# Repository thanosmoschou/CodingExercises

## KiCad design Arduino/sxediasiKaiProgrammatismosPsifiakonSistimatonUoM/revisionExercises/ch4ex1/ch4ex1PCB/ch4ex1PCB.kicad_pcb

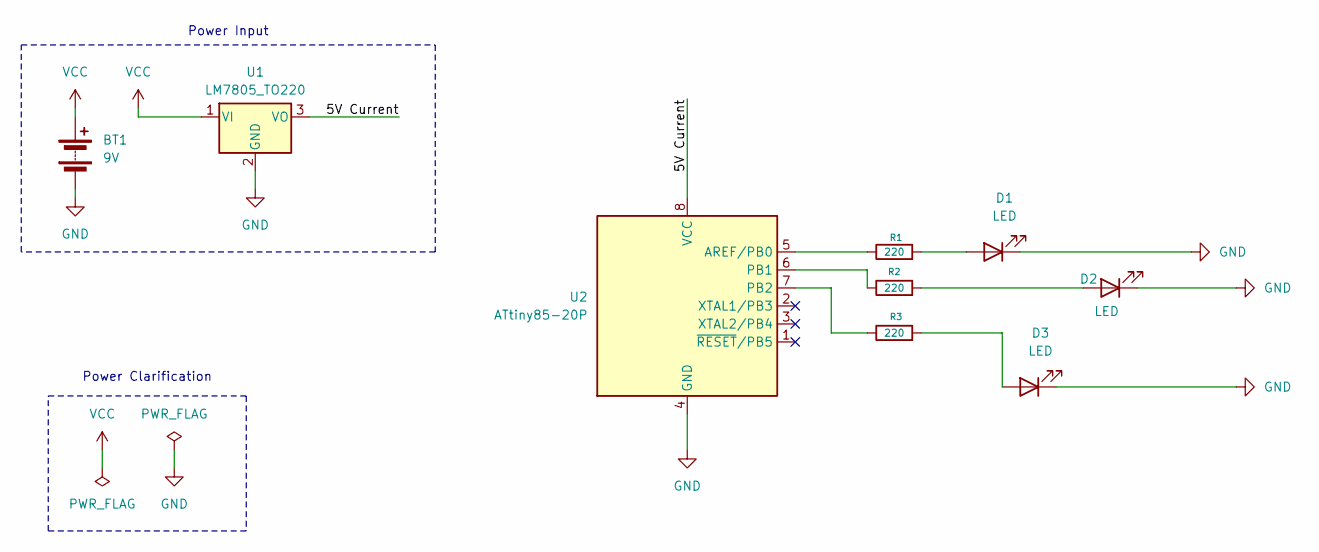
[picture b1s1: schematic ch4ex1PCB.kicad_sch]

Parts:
BT1: 9V; BatteryHolder_MPD_BA9VPC_1xPP3
D1, D2, D3: LED; LED_D5.0mm_Clear
R1, R2, R3: 220; R_Axial_DIN0207_L6.3mm_D2.5mm_P10.16mm_Horizontal
U1: LM7805_TO220; TO-220-3_Vertical
U2: ATtiny85-20P; DIP-8_W7.62mm

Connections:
/5V Current: U1.3 (VO), U2.8 (VCC)
GND: BT1.2 (-), D1.1 (K), D2.1 (K), D3.1 (K), U1.2 (GND), U2.4 (GND)
unnamed: D1.2 (A), R1.2
unnamed: D2.2 (A), R2.2
unnamed: D3.2 (A), R3.2
unnamed: R1.1, U2.5 (AREF/PB0)
unnamed: R2.1, U2.6 (PB1)
unnamed: R3.1, U2.7 (PB2)
VCC: BT1.1 (+), U1.1 (VI)

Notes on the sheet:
Power Clarification
Power Input

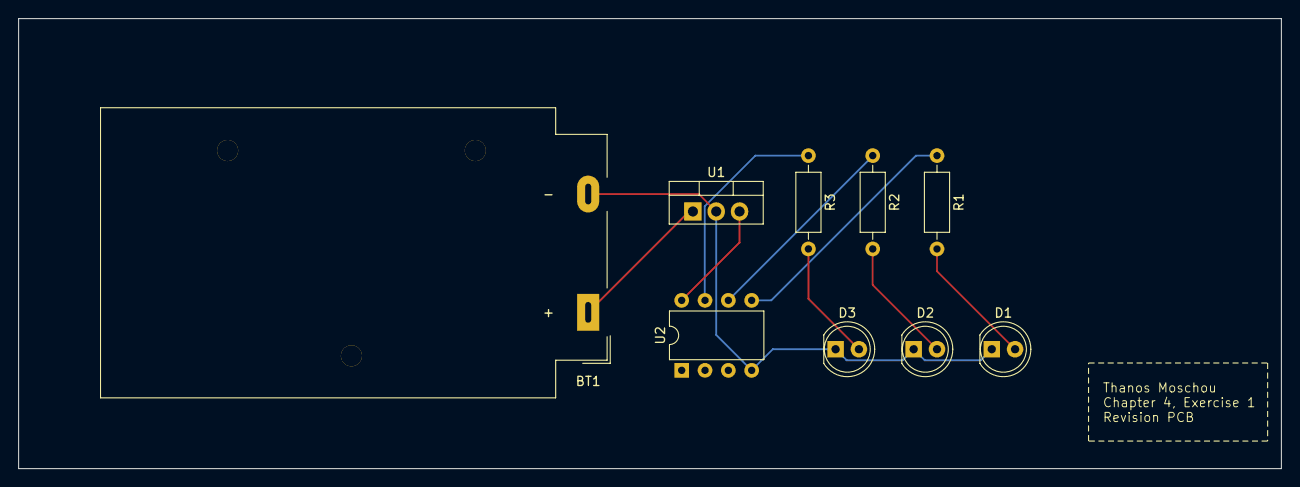
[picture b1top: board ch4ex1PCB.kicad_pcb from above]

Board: 2 copper layers, 137.5 x 49.0 mm, 9 parts (0 on the bottom side), 9 nets.

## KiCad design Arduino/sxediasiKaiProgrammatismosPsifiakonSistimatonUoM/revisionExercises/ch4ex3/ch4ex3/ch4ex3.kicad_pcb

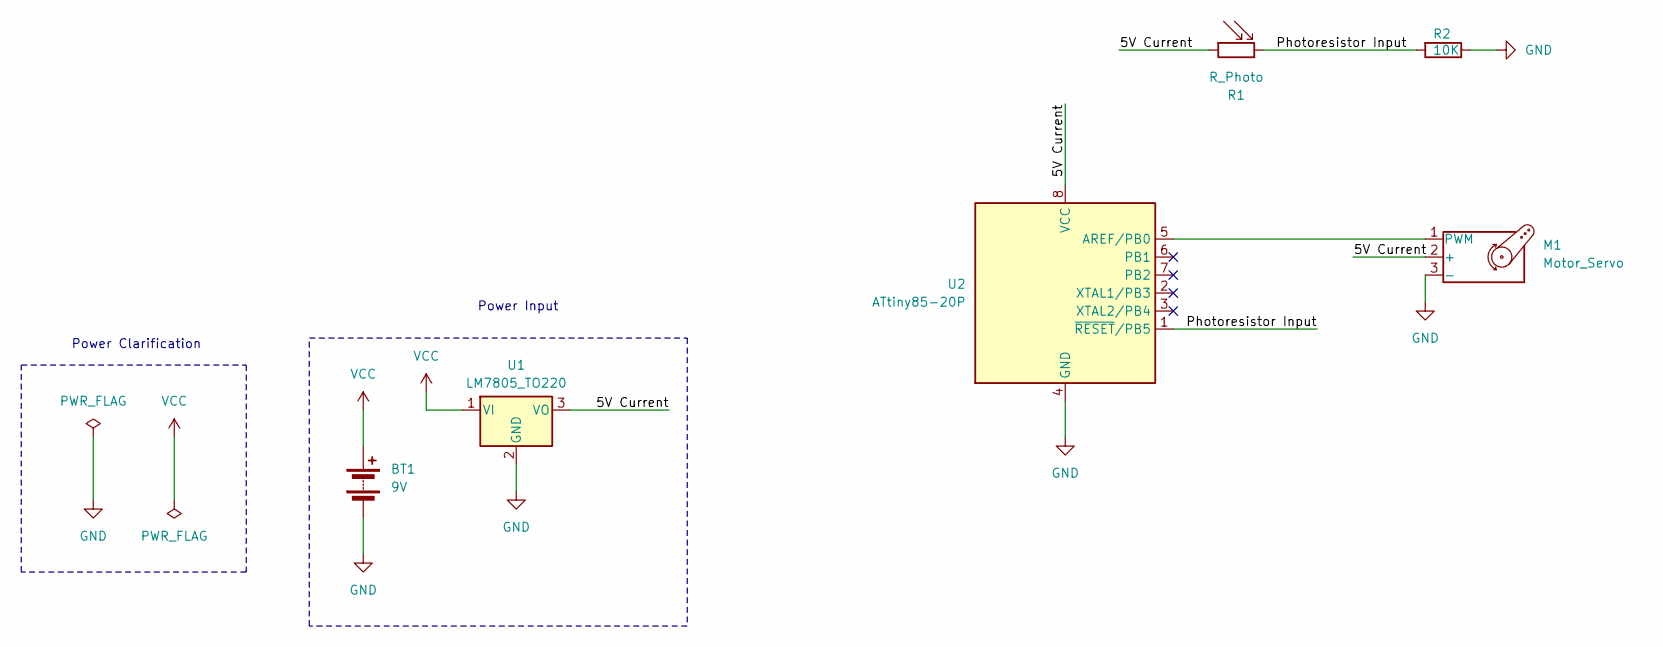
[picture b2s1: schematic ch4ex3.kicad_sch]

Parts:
BT1: 9V; BatteryHolder_MPD_BA9VPC_1xPP3
M1: Motor_Servo; PinHeader_1x03_P2.54mm_Horizontal
R1: R_Photo; Luna_NSL-32
R2: 10K; R_Axial_DIN0207_L6.3mm_D2.5mm_P10.16mm_Horizontal
U1: LM7805_TO220; TO-220-3_Vertical
U2: ATtiny85-20P; DIP-8_W7.62mm

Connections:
/5V Current: M1.2 (+), R1.1, U1.3 (VO), U2.8 (VCC)
/Photoresistor Input: R1.2, R2.2, U2.1 (~RESET/PB5)
GND: BT1.2 (-), M1.3 (-), R2.1, U1.2 (GND), U2.4 (GND)
unnamed: M1.1 (PWM), U2.5 (AREF/PB0)
VCC: BT1.1 (+), U1.1 (VI)

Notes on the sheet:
Power Clarification
Power Input

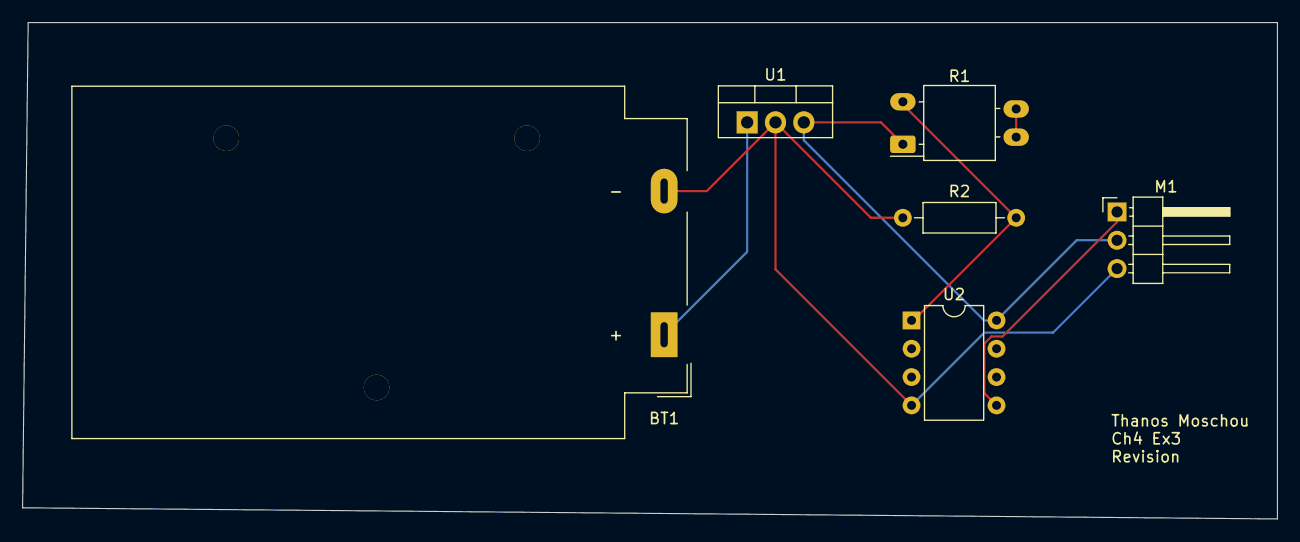
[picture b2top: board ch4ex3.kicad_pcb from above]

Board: 2 copper layers, 112.5 x 44.5 mm, 6 parts (0 on the bottom side), 5 nets.

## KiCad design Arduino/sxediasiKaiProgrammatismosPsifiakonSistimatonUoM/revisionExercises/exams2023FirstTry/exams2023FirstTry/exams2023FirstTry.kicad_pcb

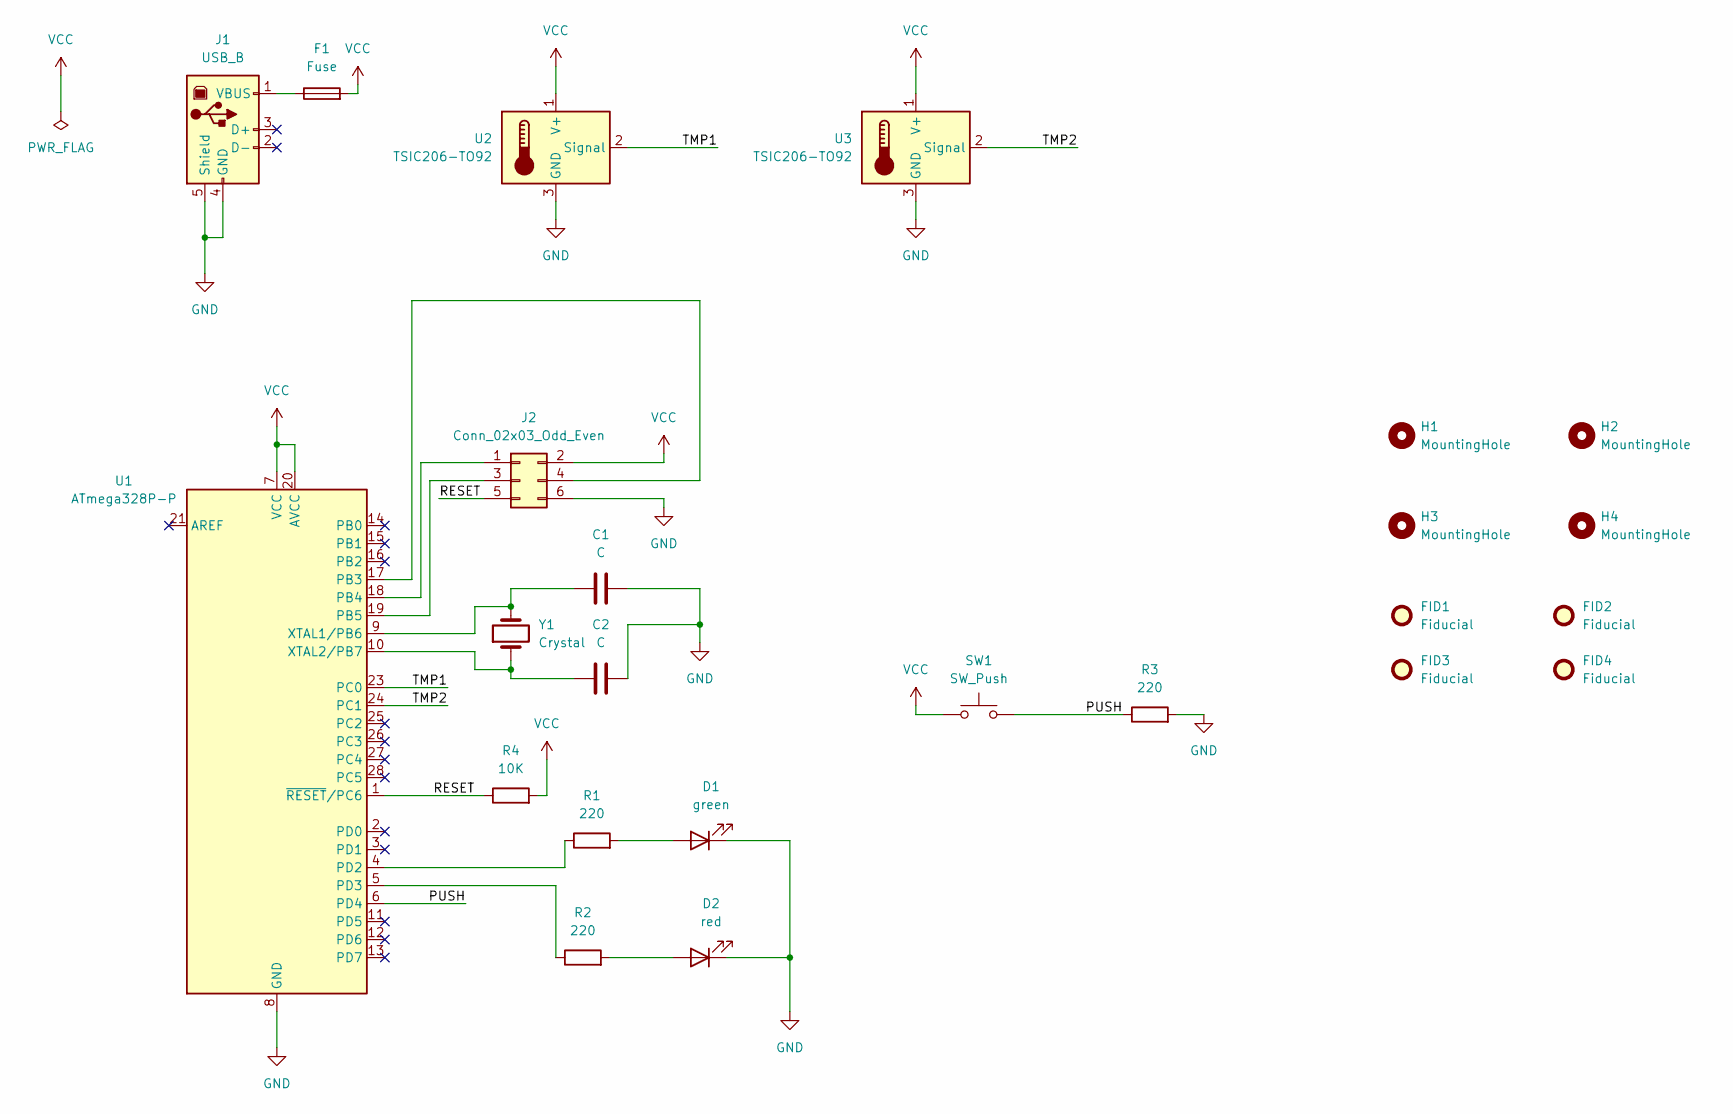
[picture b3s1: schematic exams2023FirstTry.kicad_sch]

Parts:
C1, C2: C; C_0805_2012Metric
D1: green; LED_D5.0mm_Clear
D2: red; LED_D5.0mm_Clear
F1: Fuse; Fuse_1812_4532Metric
FID1, FID2, FID3, FID4: Fiducial; Fiducial_1mm_Mask2mm
H1, H2, H3, H4: MountingHole; MountingHole_3.2mm_M3
J1: USB_B; USB_B_OST_USB-B1HSxx_Horizontal
J2: Conn_02x03_Odd_Even; PinHeader_2x03_P2.54mm_Vertical
R1, R2, R3: 220; R_Axial_DIN0207_L6.3mm_D2.5mm_P10.16mm_Horizontal
R4: 10K; R_Axial_DIN0207_L6.3mm_D2.5mm_P10.16mm_Horizontal
SW1: SW_Push; SW_Push_1P1T_XKB_TS-1187A
U1: ATmega328P-P; DIP-28_W7.62mm
U2, U3: TSIC206-TO92; TO-92_Inline
Y1: Crystal; Crystal_HC49-4H_Vertical

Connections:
/PUSH: R3.1, SW1.2, U1.6 (PD4)
/RESET: J2.5, R4.1, U1.1 (~RESET/PC6)
/TMP1: U1.23 (PC0), U2.2 (Signal)
/TMP2: U1.24 (PC1), U3.2 (Signal)
GND: C1.2, C2.2, D1.1 (K), D2.1 (K), J1.4 (GND), J1.5 (Shield), J2.6, R3.2, U1.8 (GND), U1.22 (GND), U2.3 (GND), U3.3 (GND)
unnamed: D1.2 (A), R1.2
unnamed: D2.2 (A), R2.2
unnamed: F1.1, J1.1 (VBUS)
unnamed: J2.1, U1.18 (PB4)
unnamed: J2.3, U1.19 (PB5)
unnamed: J2.4, U1.17 (PB3)
unnamed: R1.1, U1.4 (PD2)
unnamed: R2.1, U1.5 (PD3)
unnamed: C1.1, U1.9 (XTAL1/PB6), Y1.2
unnamed: C2.1, U1.10 (XTAL2/PB7), Y1.1
VCC: F1.2, J2.2, R4.2, SW1.1, U1.7 (VCC), U1.20 (AVCC), U2.1 (V+), U3.1 (V+)

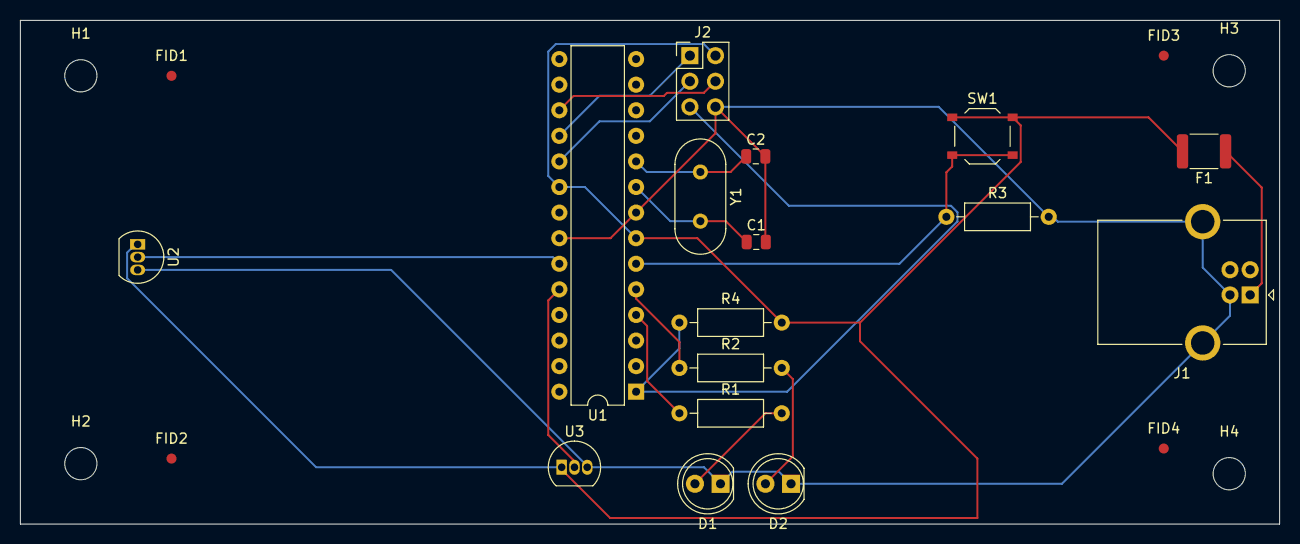
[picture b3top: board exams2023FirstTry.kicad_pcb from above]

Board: 2 copper layers, 125.0 x 50.0 mm, 24 parts (0 on the bottom side), 16 nets.

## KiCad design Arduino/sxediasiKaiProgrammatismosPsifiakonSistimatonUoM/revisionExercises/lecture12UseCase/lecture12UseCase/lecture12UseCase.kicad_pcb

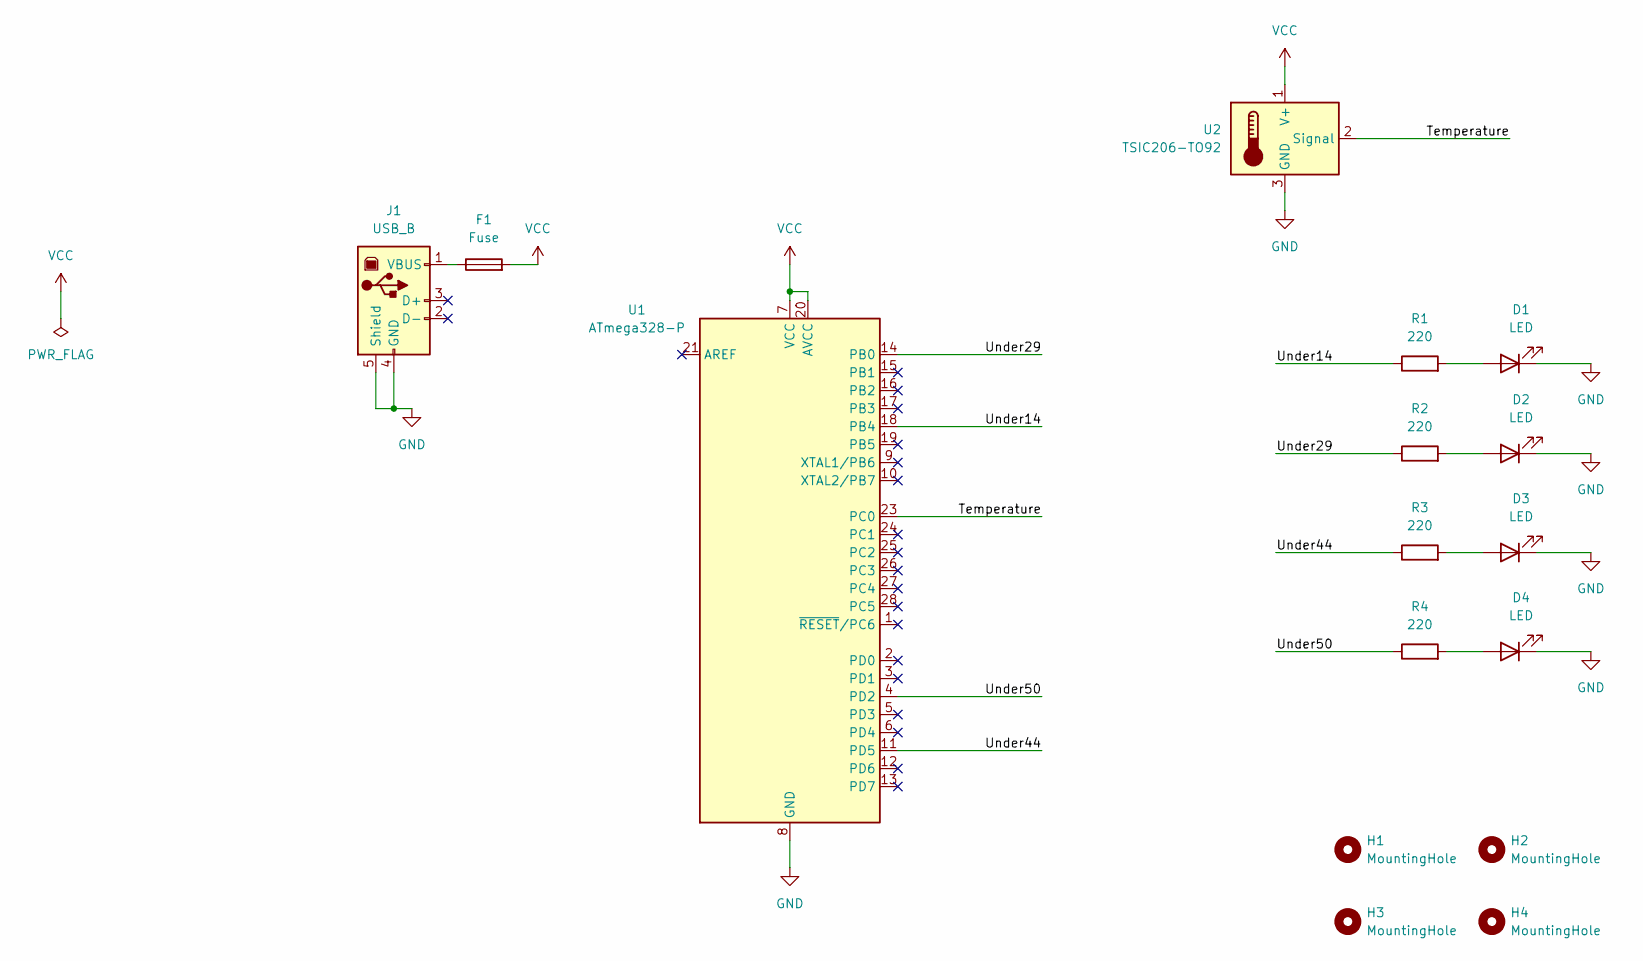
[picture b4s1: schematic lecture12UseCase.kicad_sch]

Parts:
D1, D2, D3, D4: LED; LED_D5.0mm_Clear
F1: Fuse; Fuse_0402_1005Metric
H1, H2, H3, H4: MountingHole; MountingHole_3.2mm_M3_Pad
J1: USB_B; USB_B_Amphenol_MUSB-D511_Vertical_Rugged
R1, R2, R3, R4: 220; R_Axial_DIN0207_L6.3mm_D2.5mm_P10.16mm_Horizontal
U1: ATmega328-P; DIP-28_W7.62mm
U2: TSIC206-TO92; TO-92_Inline

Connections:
/Temperature: U1.23 (PC0), U2.2 (Signal)
/Under14: R1.1, U1.18 (PB4)
/Under29: R2.1, U1.14 (PB0)
/Under44: R3.1, U1.11 (PD5)
/Under50: R4.1, U1.4 (PD2)
GND: D1.1 (K), D2.1 (K), D3.1 (K), D4.1 (K), J1.4 (GND), J1.5 (Shield), U1.8 (GND), U1.22 (GND), U2.3 (GND)
unnamed: D1.2 (A), R1.2
unnamed: D2.2 (A), R2.2
unnamed: D3.2 (A), R3.2
unnamed: D4.2 (A), R4.2
unnamed: F1.1, J1.1 (VBUS)
VCC: F1.2, U1.7 (VCC), U1.20 (AVCC), U2.1 (V+)

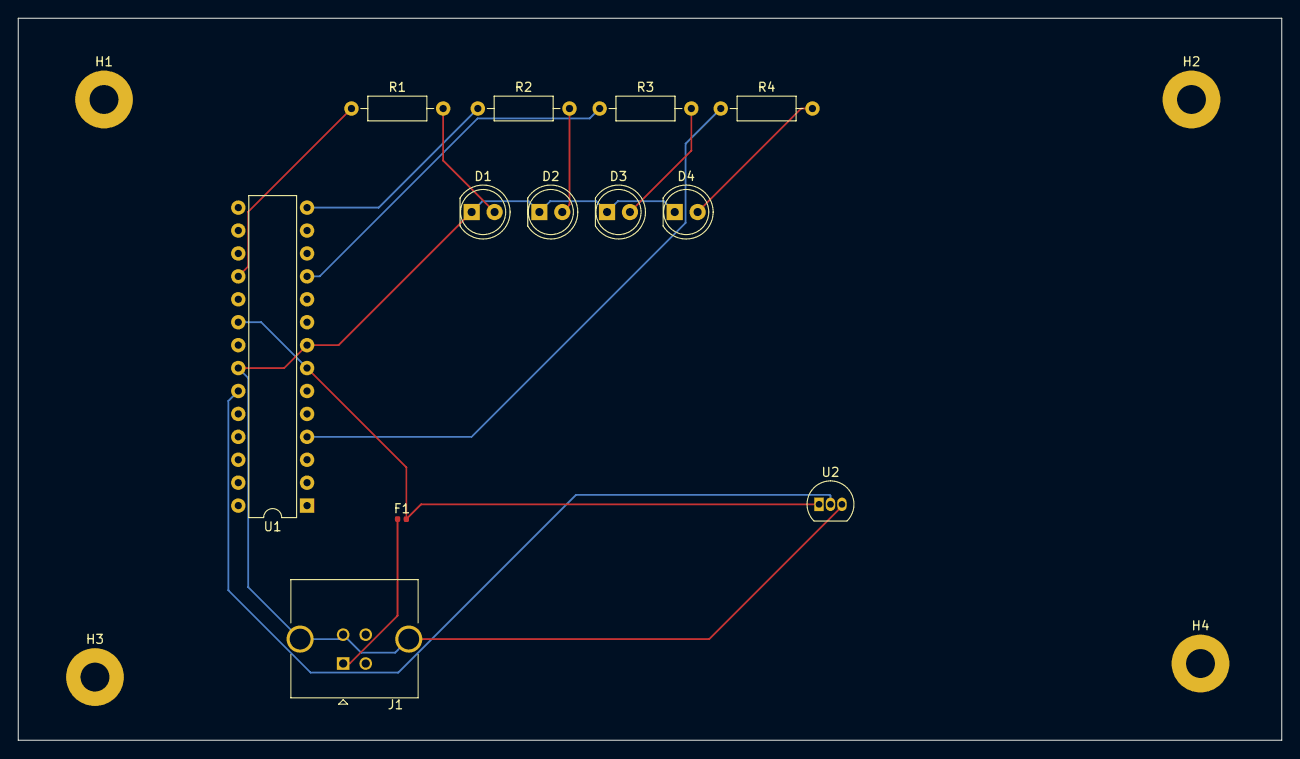
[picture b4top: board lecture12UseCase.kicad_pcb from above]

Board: 2 copper layers, 140.0 x 80.0 mm, 16 parts (0 on the bottom side), 12 nets.
